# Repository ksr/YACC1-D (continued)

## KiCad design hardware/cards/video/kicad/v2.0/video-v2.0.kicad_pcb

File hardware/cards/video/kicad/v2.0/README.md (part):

# video-v2.0 — KiCad design master for the video card

**The master since 2026-10-22. Ready to order since 2026-10-23 (re-reviewed, every re-review finding applied); not
ordered. Revised 2026-10-26 before the order: the DB9's VSYNC polarity jumper JP4** (below), the board routed again
2026-10-27, with the board-layout rules' silkscreen and cottageworker.com on it; the gerbers exported again
2026-11-03 with every part's value on the silk (silk only) and, the same day, with each power plane in one piece
(16 power pads connected solid, inner layers only: "Planes (2026-11-03)"; `video-v2.0-gerbers.zip`, what to upload:
"Ordering" below). V2.0 is the v1.3 card (`../v1.3/`: 6845, IDT7134 text RAM,
the DOTS jumper, 12 MHz, both fonts in one character generator) plus a **graphics layer**, **every register on I/O ports
PA-PE** and **two PS/2 ports** on an ATmega328P with an **INT jumper**. The design note is `BACKLOG.md` "Video card
V2.0"; the theory `docs/cards/video-v2.md`; the ATmega's firmware `embedded/video-ps2`; the picture and the CPU
side `tools/vidsim.py --card v2.0`.

**Revised 2026-10-22 after the design review** (`hardware/cards/video/reviews/v2.0.md`, its status table at the top):
every HIGH and MEDIUM finding is in the circuit or the firmware, and two features were added - **direct mode** (with
GFX-ON = 0 the CPU owns the graphics RAM: a plain SRAM at any clock the machine runs) and the **text-only build** (the
graphics chips left off, a status bit saying so). **Re-reviewed 2026-10-23** (`hardware/cards/video/reviews/v2.0-r2.md`,
HIGH 0, MED 1, LOW 9, INFO 6; its status table at the top): the MD-60SM side-leg slots widened (R2-1), IC55's socket
clear of its neighbours (R2-2), the bus -RESET buffered (R2-3), the BOM, the README's statements, the silkscreen, the
timing test and the firmware; the rest are driver rules and bench measurements.

Unlike v1.x (Eagle conversions edited in KiCad) this design is **generated**: `v20_netlist.py` is the circuit,
`gen_v20.py` draws the schematic (since 2026-10-24 a root sheet and eight functional sheets with the nets drawn as
wires: "The schematic" below), builds the board and writes `BOM.md`; `build.sh` routes and checks it. Change the circuit in
`v20_netlist.py`, the placement in `gen_v20.py` (`PLACE`), then run `./build.sh` (KiCad 10, Freerouting 1.9 in `FRJAR`,
default `~/freerouting/freerouting.jar`, which opens a window while it runs; `SEEDS="..."` and `MP=` choose the
component orders and passes). `tools/eagle_to_kicad_all.py` never writes here (`MASTER` marker).

## The board

- **218.42 x 113.97 mm** (x 17.747-236.167): the blank V3.2 card's outline lengthened to the sequencer logic V2.1l's
  218 mm, so it needs the same slot space; X1 (DIN 41612) exactly where every card has it, copper keepouts round its
  two screws.
- **4 layers**, the v1.3 / memory card v2.0 stack-up and rules: In1.Cu a solid GND plane, In2.Cu a solid VCC plane, GND
  and VCC never routed (every power pin is a through-hole pad on its plane); signals 0.25 mm, clearance 0.2 mm, vias
  0.8 / 0.4 mm.
- **Placement** (`gen_v20.py` `PLACE`; pin 1 of every DIP at the top left, each 100 nF beside its IC's VCC pin):
  row A (top) the port decode, strobes, the inverters IC46 (beside the control register they mostly serve), the control
  register, status buffers, the PS/2 and graphics latches, WRQ and the video driver IC27; on the left the 600-mil parts (IC15 text RAM, IC17 6845, IC39 62256, IC25 28C64) and IC18 with SV3 /
  RN2; row B the graphics address muxes, display latch and shifter, the ATmega, with the GD pull-ups RN3 standing between
  IC38 and IC42; under IC42 / IC43, on its side, the direct-mode read buffer IC55 (the band under the muxes is left to
  the routing); row C the text pipeline and the gates, with the text-only pads R25 / R26 in the gaps beside IC1; row D
  the clock chain (IC28, IC21, IC20 with Q2, SV4), the remaining gates (IC32 among them, beside the counter whose QC and
  RCO it ORs) and IC54 (turned round, beside J4); the right
  edge DB9 (X2) with its VSYNC polarity jumper JP4 standing beside it (2026-10-26), RCA (J1), the keyboard (J2) and mouse (J3) Mini-DINs with their faces at the board edge, F1, the FTDI header J4 (a legend
  at every pin), the PWR LED. `gen_v20.py place` checks that no two courtyards overlap and, since the re-review (R2-2),
  that every DIP **socket** fits: each socket's outline (the pin rows + 1.3 mm at the sides, the end pins + 1.9 mm at
  the ends: the widest stamped sockets) clear of every other socket and of every other part's pads and body. The
  closest are IC55 (on its side between IC42 above and IC19 / IC1 below) with 0.02 mm to IC42's and 0.10 to IC19's /
  IC1's, IC55 / C59 0.17, IC49 / R12 0.17, IC25 / IC39 0.18 mm; with turned-pin sockets (1.27 mm end walls) IC55 has
  ~0.65 mm. RN3 and C59 stand 0.3 mm left of the middle of their gap for it.
- **Silkscreen** (R2-9; the board-layout rules since 2026-10-24, below): `gen_v20.py silk` writes every legend afresh
  and places it and every reference clear of the other silk, the pads, the edge and every part's body, its own
  included (`silk_texts()`, `silk_place()`). Each IC's type stands on the reference's line ("IC30 74LS138"); the
  jumpers and the LED carry their function and the jumpers each position's meaning. The jack legends "KEYBOARD (PURPLE)" and
  "MOUSE (GREEN)" stand turned beside each jack's body; the Mini-DIN outline is broken round its side-leg pads and stops
  short of the board edge. The card's name stands in the band under the graphics muxes. Since 2026-11-03 every
  resistor, network, capacitor, crystal and the fuse carries its value beside its reference ("R10 1k", "RN3 10k x8",
  "C16 47u", "Y1 16MHz", "F1 0.5A").

## The board-layout rules (2026-10-24)

The rules for every YACC1 board (switches, buttons, LEDs and outside-cable connectors on the front edge, the edge
farthest from the bus connector; every reference readable with the parts fitted, never under a chip, socket or module,
an IC's type beside it; every switch, button and LED labelled with its function, each position of a switch with what
it selects) came after this board was routed and before it was ordered. V2.0 took them on the **silkscreen only**
(2026-10-24): no part moved, the copper and the drills stayed the route of 2026-10-23 (`ed7c060`, order 5, 285 vias).
The VSYNC jumper JP4 (2026-10-26) follows them too: a jumper block near the front edge, its positions labelled. The
board was routed afresh for it ("Results"). Every part's value beside its reference (2026-11-03) came the same way,
on the silkscreen only ("Part values" below).

| Rule | On this board |
|---|---|
| front edge | the DB9 X2, the RCA J1, the PS/2 jacks J2 / J3 and the PWR LED stand at the right-hand edge, opposite X1; the DB9's VSYNC jumper JP4 stands beside the DB9. The FTDI header J4 (the ATmega's programming port) stays where it is, 24 mm in from that edge, with its pin legend: moving it would mean a new route |
| IC type beside the reference | all 40 ICs, on one line with the reference ("IC30 74LS138"): the value of each as the parts list has it, the grade included - IC17 **HD68B45SP / MC68B45P**, IC25 **AT28C64B-15**, IC49 **ATmega328P-P** (2026-11-10; "6845", "28C64" and "ATmega328P" before). Above the IC where there is room, else below it, else turned in the gap beside it (IC19, IC28, IC49 on the left, IC53 on the right); IC49's, too long for its gap on one line, stands there on two ("Labels" below) |
| no reference under a part | every text is kept off every part's body, its own included (its ink off the bodies below, and since 2026-11-10 its whole text box off every part's Fab outline, as `pcb-check` measures it): a DIP's body is the outline of the widest stamped socket (`socket_check`: the pin rows + 1.3 mm, the end pins + 1.9 mm), X1's the DIN 41612 housing (its silk, pads and 2.5 mm past its ends), J1's its outline and pads. R10, R25, R26 and R27 had their references inside their own outline: they now stand beside it. X1's reference left the housing's end (at the top-left corner, x 18.9, y 16.1, until 2026-11-10; now beside the housing with its type, "X1 DIN41612 96"); J1's, hidden by the RCA library footprint, is shown left of the jack. Checked by the texts' ink against every body and socket outline: before, 37 references stood on one - 26 capacitors' on a neighbouring IC's socket wall, IC1's on IC55's socket, IC19's, IC25's and IC54's on their own socket, J2's on J1, R15's and RN3's on IC25's / IC38's socket, R10's, R25's, R26's and R27's on their own body; now none |
| functions and positions | **LED1 PWR**. **JP2 DOTS**, "ON=8 OFF=6" (fitted: 8 dots a character, 64 x 24 with graphics; open: 6 dots, 80 x 24). **JP3 INT-EN**, "ON: PS/2 -INT" / "OFF: NO -INT" (fitted: IC27/D's open collector drives the bus -INT; open: the card never touches -INT). **SV3 BLOCK**, "A15" .. "A12" beside the pairs 1-2 .. 7-8 and "ON=0" (each pair sets the address bit the board select IC18 compares, fitted = 0, open = 1 through RN2; $D000 = 5-6 only). **SV4 DOTCLK**, "XTAL" over pin 1 and "XTAL/2" over pin 3 (1-2: DOTCLOCK the crystal; 2-3: half of it). **JP4 VSYNC**, "+VS CGA" beside pin 1 and "-VS MDA" beside pin 3 (1-2: DB9 pin 9 positive VSYNC, a TV-rate or CGA monitor; 2-3: negative, an MDA monitor; 2026-10-26). The meanings are those of `v20_netlist.py` and `docs/cards/video.md` (sections 3.1, 3.4) and `docs/cards/video-v2.md` |
| part values (2026-11-03) | all 69 resistors, networks, capacitors, crystals and the fuse: the value beside the reference, from `v20_netlist.py` (C16 **47u** for 47u 16V, F1 **0.5A** for 0.5A PTC). 63 on one line or stacked with the reference beside the part; C34 and C38 with the reference beside the part and the value next to it; C3 and C20 with the reference beside the part and the value in the legend "C3 C20: 100n" right of IC55 (no room beside them); C27 and C58 as one block beside their part's neighbour (below) |
| text size | every reference and legend 1.0 mm high with 0.15 mm strokes, JLCPCB's standard legend (the card's name 1.5 mm); "DOTS", "INT-EN" and "TEXT-ONLY" were 0.8 mm. X1's library pin numbers "1" and "32" stay 0.8 mm (0.15 mm strokes; at 1.0 mm "32" meets the housing's outline), JLCPCB's high-precision legend size |

`gen_v20.py silk` places the texts by their ink (not KiCad's taller text box), 0.15 mm from other silk (1.0 mm after an
IC's label), 0.2 mm from pads, 0.4 mm from the edge; an IC's label goes above it, else below, else turned in the gap at
its right, then its left, along that side and within its length. A second run leaves every text where it is.

**Part values (2026-11-03).** The rule for every new card (every part's type or value beside its reference, never
under a fitted part) reached V2.0 as a silkscreen change only, like the rules of 2026-10-24: no part moved, copper and
drills as routed 2026-10-27. Each resistor's, network's, capacitor's, crystal's and the fuse's value is its
`COMPANION` text, placed with the reference by `silk_place()` in this order: on one line or stacked, beside the part
(along one of its sides, within its length); else the reference beside the part and the value beside it too, nearest
the reference; else the value next to the reference wherever that is clear; else the reference beside the part and
the value in a legend with the others' that found no room ("C3 C20: 100n"); else the block at the nearest clear place.
A passive's reference and a value standing apart from it must be nearer their own part than any other non-IC part, so
no text reads as a neighbour's label. A part that ends past the first step is placed earlier in another round (after
the ICs), and the round with the fewest such parts is kept. `gen_v20.py silk` prints the parts that did not take the
first step: C34 and C38 (value apart), C3 and C20 (legend). Adding the values on the first try (the block beside the
part or anywhere) sent ten references 4-14 mm from their parts, C34's beside C52's capacitor among them; the steps
above keep every reference at its own part except two:

- **C27** (IC26's capacitor, between IC26's label, IC55's socket wall and IC19's turned label): "C27 100n" stands
  left of C59's capacitor, under "C59 100n", 3 mm above-left of C27; its reference stood there before too.
- **C58** (IC54's capacitor, at the bottom edge between R10 and IC54's label): "C58 100n" stands under R10, ending at
  C58's left end; its reference stood under R10's end before too, and R10's "R10 1k" stands turned at that end.

Both are 100n like every capacitor round them. No IC label, jumper text or legend moved: their places are those of
2026-10-24 / 2026-10-27, checked text by text.

**Proofs (2026-10-24)**, the silkscreen placed again on the committed board and nothing else rebuilt (no Freerouting,
no `build.sh`):

| Check | Result |
|---|---|
| the board, item by item (pcbnew: 120 footprints' place, orientation, value and footprint; 1,040 pads with their nets, sizes and drills; 5,069 tracks and vias; the zones and keepouts; the outline) | **identical**; the file's changes are the silkscreen texts and the reference fields' places and sizes |
| Gerbers (the commands under "Ordering"), against the export of 2026-10-23 | **only `video-v2.0-F_Silkscreen.gbr` differs**; F_Cu, In1_Cu, In2_Cu, B_Cu, F_Mask, B_Mask, B_Silkscreen, Edge_Cuts, the PTH and NPTH drill files, both drill maps and the job file are identical apart from their date lines |
| `tools/kicad/compare_netlists.py` (schematic vs board) | **MATCH, 216 of 216** net groups |
| `gen_v20.py verify` | **PASS**, 189 key connections |
| `gen_v20.py place` | 120 footprints clear; **sockets PASS** (40), the closest IC42 / IC55 0.02 mm as before |
| DRC (`reports/drc.json`) | 0 unconnected, schematic parity 0, no copper findings; **silk_overlap 0, silk_over_copper 8, silk_edge_clearance 8** (J1's, X1's and X2's library outlines, as before), text_height / text_thickness 0 |
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
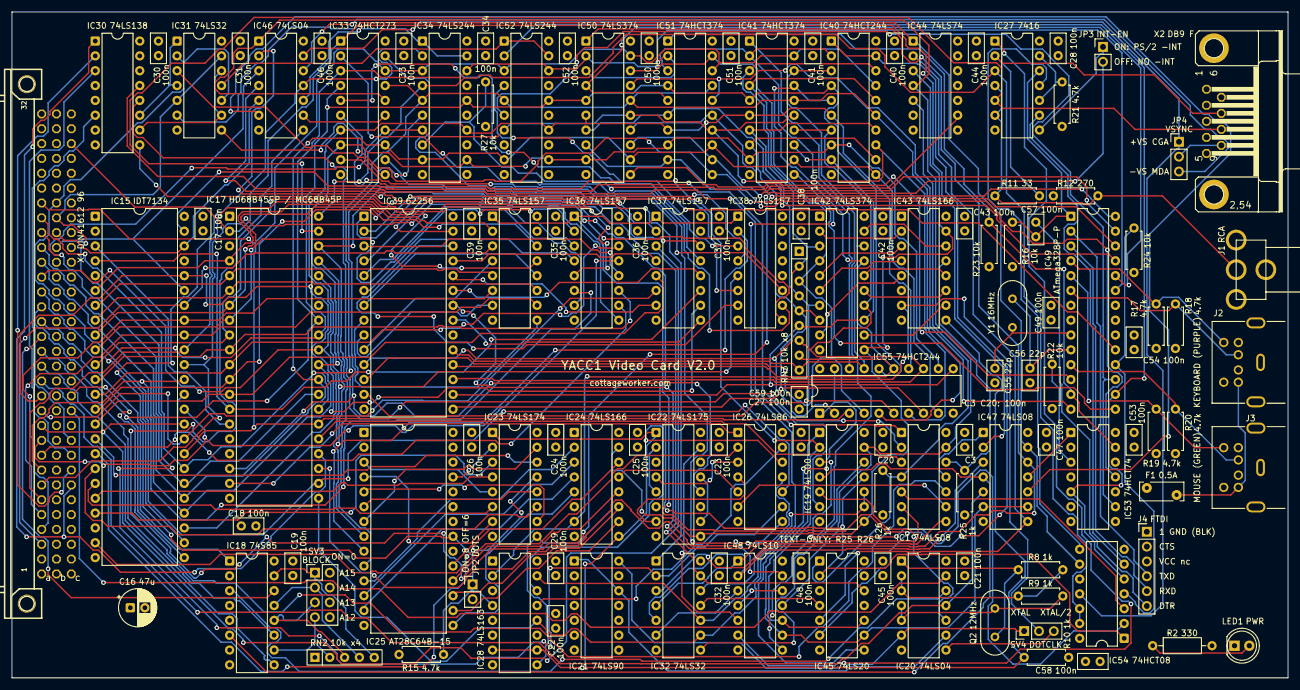
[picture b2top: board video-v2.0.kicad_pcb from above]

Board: 4 copper layers, 218.4 x 114.0 mm, 121 parts (0 on the bottom side), 219 nets.

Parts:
C3, C17, C18, C19, C20, C21, C22, C23, C24, C25, C26, C27, C28, C29, C30, C31, C32, C33, C34, C35, C36, C37, C38, C39, C40, C41, C42, C43, C44, C45, C46, C47, C48, C49, C50, C51, C52, C53, C54, C57, C58, C59: 100n; C_Disc_D5.0mm_W2.5mm_P2.50mm
C16: 47u 16V; CP_Radial_D6.3mm_P2.50mm
C55, C56: 22p; C_Disc_D5.0mm_W2.5mm_P2.50mm
F1: 0.5A PTC; Fuse_Bourns_MF-RHT050
IC1: 74ALS08; DIP-14_W7.62mm
IC15: IDT7134; DIP-48_W15.24mm
IC17: HD68B45SP / MC68B45P; DIP-40_W15.24mm
IC18: 74S85; DIP-16_W7.62mm
IC19: 74LS00; DIP-14_W7.62mm
IC20, IC46: 74LS04; DIP-14_W7.62mm
IC21: 74LS90; DIP-14_W7.62mm
IC22: 74LS175; DIP-16_W7.62mm
IC23: 74LS174; DIP-16_W7.62mm
IC24, IC43: 74LS166; DIP-16_W7.62mm
IC25: AT28C64B-15; DIP-28_W15.24mm
IC26: 74LS86; DIP-14_W7.62mm
IC27: 7416; DIP-14_W7.62mm
IC28: 74LS163; DIP-16_W7.62mm
IC30: 74LS138; DIP-16_W7.62mm
IC31, IC32: 74LS32; DIP-14_W7.62mm
IC33: 74HCT273; DIP-20_W7.62mm
IC34, IC52: 74LS244; DIP-20_W7.62mm
IC35, IC36, IC37, IC38: 74LS157; DIP-16_W7.62mm
IC39: 62256; DIP-28_W15.24mm
IC40, IC55: 74HCT244; DIP-20_W7.62mm
IC41, IC51: 74HCT374; DIP-20_W7.62mm
IC42, IC50: 74LS374; DIP-20_W7.62mm
IC44: 74LS74; DIP-14_W7.62mm
IC45: 74LS20; DIP-14_W7.62mm
IC47: 74LS08; DIP-14_W7.62mm
IC48: 74LS10; DIP-14_W7.62mm
IC49: ATmega328P-P; DIP-28_W7.62mm
IC53: 74HCT74; DIP-14_W7.62mm
IC54: 74HCT08; DIP-14_W7.62mm
J1: RCA
J2: KEYBOARD; MiniDIN6_MD-60SM
J3: MOUSE; MiniDIN6_MD-60SM
J4: FTDI; PinHeader_1x06_P2.54mm_Vertical
JP2: DOTS 8=ON; PinHeader_1x02_P2.54mm_Vertical
JP3: INT-EN; PinHeader_1x02_P2.54mm_Vertical
JP4: VSYNC +/-; PinHeader_1x03_P2.54mm_Vertical
LED1: PWR; LED_D5.0mm
Q2: 12MHz; Crystal_HC49-U_Vertical
R2: 330; R_Axial_DIN0207_L6.3mm_D2.5mm_P10.16mm_Horizontal
R8, R9, R10, R25, R26: 1k; R_Axial_DIN0207_L6.3mm_D2.5mm_P7.62mm_Horizontal
R11: 33; R_Axial_DIN0207_L6.3mm_D2.5mm_P7.62mm_Horizontal
R12: 270; R_Axial_DIN0207_L6.3mm_D2.5mm_P7.62mm_Horizontal
R15, R17, R18, R19, R20, R21: 4.7k; R_Axial_DIN0207_L6.3mm_D2.5mm_P7.62mm_Horizontal
R16, R22, R23, R24, R27: 10k; R_Axial_DIN0207_L6.3mm_D2.5mm_P7.62mm_Horizontal
RN2: 10k x4; R_Array_SIP5
RN3: 10k x8; R_Array_SIP9
SV3: BLOCK; PinHeader_2x04_P2.54mm_Vertical
SV4: DOTCLK; PinHeader_1x03_P2.54mm_Vertical
X1: DIN41612 96; FABC96R
X2: DB9 F; F09HP
Y1: 16MHz; Crystal_HC49-U_Vertical

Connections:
/-INT: JP3.2, X1.C13
/-IO-RD: IC26.9, IC31.5, IC31.13, IC32.2, X1.B25
/-IO-WR: IC17.22, IC26.10, IC31.2, IC31.10, X1.B26
/-MEM-RD: IC15.43, IC46.3, X1.B23
/-MEM-WR: IC15.46, IC46.5, X1.B24
/-RESET: IC17.2, IC33.1, IC44.1, IC47.13, IC54.9, X1.C30
/-VMA: IC20.13, X1.C12
/ADDR0: IC15.42, IC35.3, X1.A3
/ADDR1: IC15.41, IC35.6, X1.A4
/ADDR2: IC15.40, IC35.10, X1.A5
/ADDR3: IC15.39, IC35.13, X1.A6
/ADDR4: IC15.38, IC36.3, X1.A7
/ADDR5: IC15.37, IC36.6, X1.A8
/ADDR6: IC15.36, IC36.10, X1.A9
/ADDR7: IC15.35, IC36.13, X1.A10
/ADDR8: IC15.34, IC37.3, X1.A11
/ADDR9: IC15.33, IC37.6, X1.A12
/ADDR10: IC15.44, IC37.10, X1.A13
/ADDR11: IC20.11, IC47.5, X1.A14
/ADDR12: IC18.9, X1.A15
/ADDR13: IC18.11, X1.A16
/ADDR14: IC18.14, X1.A17
/ADDR15: IC18.1, X1.A18
/ATTR1: IC22.4, IC26.3
/ATTR2: IC22.2, IC22.5
/ATTR3: IC22.7, IC26.4
/BOARDSEL: IC18.6, IC19.4, IC47.4
/BUSY: IC49.17, IC52.6, IC53.9
/CA3: IC23.15, IC25.7
/CA4: IC23.12, IC25.6
/CA5: IC23.10, IC25.5
/CA6: IC23.7, IC25.4
/CA7: IC23.5, IC25.3
/CA8: IC23.2, IC25.25
/CG0: IC24.2, IC25.11
/CG1: IC24.3, IC25.12
/CG2: IC24.4, IC25.13
/CG3: IC24.5, IC25.15
/CG4: IC24.10, IC25.16
/CG5: IC24.11, IC25.17
/CG6: IC24.12, IC25.18
/CG7: IC24.14, IC25.19
/CHARCLOCK: IC19.8, IC22.9, IC23.9, IC24.15, IC28.9, IC42.11, IC43.15, IC44.3
/CMDCLK: IC31.8, IC51.11, IC53.11
/CNTEN: IC22.1, IC23.1, IC24.9, IC28.7, IC28.10, IC43.9, R10.1
/CNTQA: IC26.12, IC28.14
/CNTQB: IC26.13, IC28.13
/CPAGE: IC33.9, IC38.10
/CRTCCLOCK: IC17.21, IC28.12, IC32.9, IC41.11
/CRTCCS: IC1.3, IC17.25
/CRTCE: IC17.23, IC26.8
/CTLCLK: IC31.3, IC33.11
/CURSOR: IC17.19, IC26.1
/DATA0: IC15.25, IC17.33, IC33.3, IC34.18, IC40.2, IC41.2, IC50.2, IC51.3, IC52.18, IC55.18, X1.A19
/DATA1: IC15.26, IC17.32, IC33.4, IC34.16, IC40.4, IC41.5, IC50.5, IC51.4, IC52.16, IC55.16, X1.A20
/DATA2: IC15.27, IC17.31, IC33.7, IC34.14, IC40.6, IC41.6, IC50.6, IC51.7, IC52.14, IC55.14, X1.A21
/DATA3: IC15.28, IC17.30, IC33.8, IC34.12, IC40.8, IC41.9, IC50.9, IC51.8, IC52.12, IC55.12, X1.A22
/DATA4: IC15.29, IC17.29, IC33.13, IC34.9, IC40.11, IC41.12, IC50.12, IC51.13, IC52.9, IC55.9, X1.A23
/DATA5: IC15.30, IC17.28, IC33.14, IC34.7, IC40.13, IC41.15, IC50.15, IC51.14, IC52.7, IC55.7, X1.A24
/DATA6: IC15.31, IC17.27, IC33.17, IC34.5, IC40.15, IC41.16, IC50.16, IC51.17, IC52.5, IC55.5, X1.A25
/DATA7: IC15.32, IC17.26, IC33.18, IC34.3, IC40.17, IC41.19, IC50.19, IC51.18, IC52.3, IC55.3, X1.A26
/DB9VS: JP4.2, X2.9
/DE: IC17.18, IC22.12, IC34.6
/DE2: IC22.10, IC22.13
/DE3: IC22.15, IC48.5
/DOTCLKH: IC20.8, SV4.3
/DOTCLOCK: IC24.7, IC28.2, IC43.7, SV4.2
/DOTS: IC25.21, IC28.4, IC34.2, IC46.11, JP2.1, R15.2
/DPAGE: IC33.12, IC38.11
/DRDOE: IC45.8, IC55.1, IC55.19
/EIGHT: IC46.10, IC47.2
/FDTR: C57.1, J4.6
/FRX: IC49.3, J4.5
/FTX: IC49.2, J4.4
/FULL: IC49.16, IC52.2, IC53.5, IC54.5
/FULLCLR: IC47.11, IC53.1
/GA0: IC35.4, IC39.10
/GA1: IC35.7, IC39.9
/GA2: IC35.9, IC39.8
/GA3: IC35.12, IC39.7
/GA4: IC36.4, IC39.6
/GA5: IC36.7, IC39.5
/GA6: IC36.9, IC39.4
/GA7: IC36.12, IC39.3
/GA8: IC37.4, IC39.25
/GA9: IC37.7, IC39.24
/GA10: IC37.9, IC39.21
/GA11: IC37.12, IC39.23
/GA12: IC38.4, IC39.2
/GA13: IC38.7, IC39.26
/GA14: IC38.9, IC39.1
/GD0: IC39.11, IC40.18, IC41.3, IC42.3, IC55.2, RN3.2
/GD1: IC39.12, IC40.16, IC41.4, IC42.4, IC55.4, RN3.3
/GD2: IC39.13, IC40.14, IC41.7, IC42.7, IC55.6, RN3.4
/GD3: IC39.15, IC40.12, IC41.8, IC42.8, IC55.8, RN3.5
/GD4: IC39.16, IC40.9, IC41.13, IC42.13, IC55.11, RN3.6
/GD5: IC39.17, IC40.7, IC41.14, IC42.14, IC55.13, RN3.7
/GD6: IC39.18, IC40.5, IC41.17, IC42.17, IC55.15, RN3.8
/GD7: IC39.19, IC40.3, IC41.18, IC42.18, IC55.17, RN3.9
/GDA: IC1.11, IC47.1
/GDG: IC32.5, IC47.3, IC48.2
/GDOT: IC1.12, IC43.13, R25.1
/GFXON: IC1.13, IC19.13, IC33.16, IC44.4, IC46.1, IC48.11
/GL0: IC42.2, IC43.2
/GL1: IC42.5, IC43.3
/GL2: IC42.6, IC43.4
/GL3: IC42.9, IC43.5
/GL4: IC42.12, IC43.10
/GL5: IC42.15, IC43.11
/GL6: IC42.16, IC43.12
/GL7: IC42.19, IC43.14
/GOR: IC32.6, IC48.3
/GRDOE: IC19.3, IC54.2
/GSEL: IC19.1, IC45.9, IC47.6, IC47.9, IC48.9
/GWE: IC39.27, IC40.1, IC40.19, IC45.6
/GWR: IC44.2, IC45.5, IC47.8
/HSYNC: IC17.39, IC27.5, X2.8
/INTG: IC27.9, IC54.6
/INTOC: IC27.8, JP3.1
/INTREQ: IC49.18, IC54.4, R24.1
/IO-ADDR0: IC17.24, IC30.1, X1.C7
/IO-ADDR1: IC30.2, X1.C8
/IO-ADDR2: IC30.3, X1.C9
/IO-ADDR3: IC30.6, X1.C10
/KCLK: IC49.4, J2.5, R17.1
/KDAT: IC49.6, J2.1, R18.1
/LDDATA: IC49.12, IC50.11, IC53.3, R22.1
/MCLK: IC49.5, J3.5, R19.1
/MD0: IC49.23, IC50.3, IC51.2
/MD1: IC49.24, IC50.4, IC51.5
/MD2: IC49.25, IC50.7, IC51.6
/MD3: IC49.26, IC50.8, IC51.9
/MD4: IC49.27, IC50.13, IC51.12
/MD5: IC49.28, IC50.14, IC51.15
/MD6: IC49.14, IC50.17, IC51.16
/MD7: IC49.15, IC50.18, IC51.19
/MDAT: IC49.11, J3.1, R20.1
/MEMRD: IC19.2, IC45.10, IC46.4, IC48.10
/MEMWR: IC46.6, IC47.10
/MRST: C57.2, IC27.12, IC49.1, R16.1
/NADDR11: IC19.5, IC20.10
/NBOTH: IC48.4, IC48.12
/NGFX: IC32.13, IC45.12, IC46.2
/NMUX: IC19.11, IC35.1, IC36.1, IC37.1, IC38.1, IC45.2, IC54.1
/NVSYNC: IC46.12, JP4.3
/OEY: IC1.5, IC54.3
/OSCIN: IC20.1, Q2.1, R8.1
/OSCMID: IC20.2, IC20.3, R8.2, R9.1
/OSCOUT: IC20.4, IC20.5, Q2.2, R9.2
/PDOE: IC32.3, IC47.12, IC50.1
/PLANE0: IC33.2, IC37.13
/PLANE1: IC33.5, IC38.3
/PLANE2: IC33.6, IC38.6
/PS2VCC: F1.2, J2.4, J3.4
/PSEL_A: IC1.1, IC30.13
/PSEL_B: IC1.2, IC30.12
/PSEL_C: IC30.11, IC31.1, IC31.4
/PSEL_D: IC30.10, IC31.9, IC31.12
/PSEL_E: IC30.9, IC32.1
/PSTOE: IC31.11, IC52.1, IC52.19
/PWRLED: LED1.2, R2.1
/QCR: IC19.12, IC32.8
/RCO: IC19.9, IC19.10, IC28.15, IC32.10
/RDCMD: IC49.13, IC51.1, IC53.13, R23.1
/RESETB: IC27.11, IC54.8
/RESETH: IC27.10, IC27.13, R21.1
/SEL0: IC18.10, RN2.2, SV3.7
/SEL1: IC18.12, RN2.3, SV3.5
/SEL2: IC18.13, RN2.4, SV3.3
/SEL3: IC18.15, RN2.5, SV3.1
/SRC: IC49.19, IC52.4
/SRDOE: IC41.1, IC48.8
/STATOE: IC31.6, IC34.1, IC34.19
/SYNC: IC27.4, IC27.6, J1.C1, R11.1, R12.2
/TD: IC1.9, IC26.6
/TDG: IC1.8, IC32.4, IC48.1
/TDOT: IC24.13, IC26.5
/TEXTOFF: IC33.15, IC46.9
/TEXTON: IC1.10, IC46.8
/TXTCE: IC15.47, IC19.6
/TXTONLY: IC34.8, IC44.9, R27.1
/VADDR0: IC15.6, IC17.4, IC35.2
/VADDR1: IC15.7, IC17.5, IC35.5
/VADDR2: IC15.8, IC17.6, IC35.11
/VADDR3: IC15.9, IC17.7, IC35.14
/VADDR4: IC15.10, IC17.8, IC36.2
/VADDR5: IC15.11, IC17.9, IC36.5
/VADDR6: IC15.12, IC17.10, IC36.11
/VADDR7: IC15.13, IC17.11, IC36.14
/VADDR8: IC15.14, IC17.12, IC37.2
/VADDR9: IC15.15, IC17.13, IC37.5
/VADDR10: IC15.4, IC17.14, IC37.11
/VADDR11: IC15.3, IC17.15
/VDATA0: IC15.16, IC23.14
/VDATA1: IC15.17, IC23.13
/VDATA2: IC15.18, IC23.11
/VDATA3: IC15.19, IC23.6
/VDATA4: IC15.20, IC23.4
/VDATA5: IC15.21, IC23.3
/VDATA7: IC15.23, IC26.2
/VIDEO: IC27.2, R11.2, X2.7
/VIDN: IC27.1, IC48.6
/VMA: IC18.3, IC20.12
/VROWS0: IC17.38, IC25.10, IC37.14
/VROWS1: IC17.37, IC25.9, IC38.2
/VROWS2: IC17.36, IC25.8, IC38.5
/VSBUF: IC46.13, IC54.11, JP4.1
/VSYNC: IC17.40, IC27.3, IC34.4, IC54.12, IC54.13
/WEPH: IC26.11, IC32.12
/WEPH2: IC32.11, IC45.4
/WRQ: IC1.4, IC44.5, IC45.1, R26.1
/WSLOT: IC1.6, IC39.22
/XORM: IC33.19, IC48.13
/XT1: C55.1, IC49.9, Y1.1
/XT2: C56.1, IC49.10, Y1.2
/XTAL: IC20.6, IC21.14, SV4.1
/XTALDIV2: IC20.9, IC21.1, IC21.12
GND: C3.2, C16.2, C17.2, C18.2, C19.2, C20.2, C21.2, C22.2, C23.2, C24.2, C25.2, C26.2, C27.2, C28.2, C29.2, C30.2, C31.2, C32.2, C33.2, C34.2, C35.2, C36.2, C37.2, C38.2, C39.2, C40.2, C41.2, C42.2, C43.2, C44.2, C45.2, C46.2, C47.2, C48.2, C49.2, C50.2, C51.2, C52.2, C53.2, C54.2, C55.2, C56.2, C58.2, C59.2, IC1.7, IC15.1, IC15.5, IC15.24, IC15.45, IC17.1, IC17.3, IC18.2, IC18.4, IC18.8, IC19.7, IC20.7, IC21.2, IC21.3, IC21.6, IC21.7, IC21.10, IC22.8, IC23.8, IC24.1, IC24.6, IC24.8, IC25.2, IC25.14, IC25.20, IC25.22, IC25.23, IC25.24, IC26.7, IC27.7, IC28.3, IC28.5, IC28.8, IC30.4, IC30.5, IC30.8, IC31.7, IC32.7, IC33.10, IC34.10, IC34.13, IC34.17, IC35.8, IC35.15, IC36.8, IC36.15, IC37.8, IC37.15, IC38.8, IC38.13, IC38.14, IC38.15, IC39.14, IC39.20, IC40.10, IC41.10, IC42.1, IC42.10, IC43.1, IC43.6, IC43.8, IC44.7, IC44.11, IC44.12, IC44.13, IC45.7, IC46.7, IC47.7, IC48.7, IC49.8, IC49.22, IC50.10, IC51.10, IC52.8, IC52.10, IC52.11, IC52.13, IC52.15, IC52.17, IC53.7, IC54.7, IC55.10, J1.S1, J1.S2, J1.S3, J2.3, J2.S, J3.3, J3.S, J4.1, J4.2, JP2.2, LED1.1, R24.2, R25.2, R26.2, SV3.2, SV3.4, SV3.6, SV3.8, X1.A1, X1.A32, X1.B1, X1.B32, X1.C1, X1.C32, X2.1, X2.2, X2.G1, X2.G2
VCC: C3.1, C16.1, C17.1, C18.1, C19.1, C20.1, C21.1, C22.1, C23.1, C24.1, C25.1, C26.1, C27.1, C28.1, C29.1, C30.1, C31.1, C32.1, C33.1, C34.1, C35.1, C36.1, C37.1, C38.1, C39.1, C40.1, C41.1, C42.1, C43.1, C44.1, C45.1, C46.1, C47.1, C48.1, C49.1, C50.1, C51.1, C52.1, C53.1, C54.1, C58.1, C59.1, F1.1, IC1.14, IC15.2, IC15.48, IC17.20, IC18.16, IC19.14, IC20.14, IC21.5, IC22.16, IC23.16, IC24.16, IC25.27, IC25.28, IC26.14, IC27.14, IC28.1, IC28.6, IC28.16, IC30.16, IC31.14, IC32.14, IC33.20, IC34.11, IC34.15, IC34.20, IC35.16, IC36.16, IC37.16, IC38.16, IC39.28, IC40.20, IC41.20, IC42.20, IC43.16, IC44.10, IC44.14, IC45.13, IC45.14, IC46.14, IC47.14, IC48.14, IC49.7, IC49.20, IC50.20, IC51.20, IC52.20, IC53.2, IC53.4, IC53.10, IC53.12, IC53.14, IC54.10, IC54.14, IC55.20, R2.2, R10.2, R12.1, R15.1, R16.2, R17.2, R18.2, R19.2, R20.2, R21.2, R22.2, R23.2, R27.2, RN2.1, RN3.1, X1.A2, X1.A31, X1.B2, X1.B31, X1.C2, X1.C31

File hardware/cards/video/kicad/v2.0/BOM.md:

# Video card V2.0 - bill of materials

GENERATED by `gen_v20.py bom` from `v20_netlist.py` (2026-10-26) - do not edit. 121 parts. Buy every IC in a socket (the 6845, the IDT7134, the 28C64, the 62256 and the ATmega at least); the placement leaves room for stamped sockets with end walls up to 1.9 mm (R2-2, `gen_v20.py place`). **Text-only build** (the recommended first build, README): leave off the parts marked *off*, fit the ones marked *only*.

| Qty | Value | Footprint | References | Text-only | Buy / note |
|---|---|---|---|---|---|
| 30 | 100n | C_Disc_D5.0mm_W2.5mm_P2.50mm | C3, C17, C18, C19, C20, C21, C22, C23, C24, C25, C26, C27, C28, C29, C30, C31, C32, C33, C34, C46, C47, C48, C49, C50, C51, C52, C53, C54, C57, C58 |  | ceramic X7R, 50 V, 2.5 mm lead spacing |
| 1 | 47u 16V | CP_Radial_D6.3mm_P2.50mm | C16 |  | 47 uF electrolytic, 16 V or more, radial 6.3 mm, 2.5 mm pitch (R2-7) |
| 12 | 100n | C_Disc_D5.0mm_W2.5mm_P2.50mm | C35, C36, C37, C38, C39, C40, C41, C42, C43, C44, C45, C59 | off | ceramic X7R, 50 V, 2.5 mm lead spacing |
| 2 | 22p | C_Disc_D5.0mm_W2.5mm_P2.50mm | C55, C56 |  | ceramic C0G (NP0), 50 V, 2.5 mm lead spacing |
| 1 | 0.5A PTC | Fuse_Bourns_MF-RHT050 | F1 |  | Bourns MF-RHT050 (0.5 A hold, radial) |
| 1 | 74ALS08 | DIP-14_W7.62mm | IC1 |  |  |
| 1 | IDT7134 | DIP-48_W15.24mm | IC15 |  | IDT7134 (SA/LA, 55-90 ns, DIP-48), or the V1.0 card's chip |
| 1 | HD68B45SP / MC68B45P | DIP-40_W15.24mm | IC17 |  | HD68B45SP (Hitachi) or MC68B45P (Motorola), the 2 MHz (B) bus grade: a 6 MHz CPU's OUT gives E 333 ns high (PWEH 220 ns in the B grade, 450 in the 1 MHz grade) and 6-dot mode needs its clock-low time (V2-11, R2-7). HD6845SP / MC6845P (the 1 MHz grades) only with a 1 MHz CPU and the V2-11 clock-low check in 6-dot mode. Hitachi's letters (HD6845S / HD68A45S / HD68B45S = 1.0 / 1.5 / 2.0 MHz) to verify on the part's data sheet |
| 1 | 74S85 | DIP-16_W7.62mm | IC18 |  | 74S85 (the V1.x card's; a 74LS85 also works: see the README) |
| 1 | 74LS00 | DIP-14_W7.62mm | IC19 |  | 74LS00; a 74ALS00 adds a little more CHARCLOCK margin (R3-1) |
| 2 | 74LS04 | DIP-14_W7.62mm | IC20, IC46 |  |  |
| 1 | 74LS90 | DIP-14_W7.62mm | IC21 |  |  |
| 1 | 74LS175 | DIP-16_W7.62mm | IC22 |  |  |
| 1 | 74LS174 | DIP-16_W7.62mm | IC23 |  |  |
| 1 | 74LS166 | DIP-16_W7.62mm | IC24 |  |  |
| 1 | AT28C64B-15 | DIP-28_W15.24mm | IC25 |  | AT28C64B-15PU (Microchip), 150 ns, burned with chargen-v20.bin (minipro -p AT28C64B -u -P -w) |
| 1 | 74LS86 | DIP-14_W7.62mm | IC26 |  |  |
| 1 | 7416 | DIP-14_W7.62mm | IC27 |  |  |
| 1 | 74LS163 | DIP-16_W7.62mm | IC28 |  | 74F163A or 74ALS163B (same pinout; R3-1: with a 74LS163, CHARCLOCK's set-up to the 74LS166s' SH/-LD is ~3 ns at worst-case delays, ~24 ns typical); keep a spare 74F163 |
| 1 | 74LS138 | DIP-16_W7.62mm | IC30 |  |  |
| 2 | 74LS32 | DIP-14_W7.62mm | IC31, IC32 |  |  |
| 1 | 74HCT273 | DIP-20_W7.62mm | IC33 |  |  |
| 2 | 74LS244 | DIP-20_W7.62mm | IC34, IC52 |  |  |
| 4 | 74LS157 | DIP-16_W7.62mm | IC35, IC36, IC37, IC38 | off |  |
| 1 | 62256 | DIP-28_W15.24mm | IC39 | off | AS6C62256-55PCN (Alliance, 55 ns, 600-mil DIP-28): -55 recommended (current production); a slower 62256 works in direct mode up to the machine's 6 MHz and in slot mode in 8-dot mode (R2-8); not a 300-mil 'skinny' 62256 |
| 1 | 74HCT244 | DIP-20_W7.62mm | IC40 | off |  |
| 1 | 74HCT374 | DIP-20_W7.62mm | IC41 | off | 74HCT374; a 74ACT374 (24 mA) if DATA0's low level during a window read is above 0.5 V (R2-6) |
| 1 | 74LS374 | DIP-20_W7.62mm | IC42 | off |  |
| 1 | 74LS166 | DIP-16_W7.62mm | IC43 | off |  |
| 1 | 74LS74 | DIP-14_W7.62mm | IC44 | off |  |
| 1 | 74LS20 | DIP-14_W7.62mm | IC45 | off |  |
| 1 | 74LS08 | DIP-14_W7.62mm | IC47 |  |  |
| 1 | 74LS10 | DIP-14_W7.62mm | IC48 |  |  |
| 1 | ATmega328P-P | DIP-28_W7.62mm | IC49 |  | ATmega328P-PU with the Arduino Uno bootloader burned (ISP) before fitting |
| 1 | 74LS374 | DIP-20_W7.62mm | IC50 |  |  |
| 1 | 74HCT374 | DIP-20_W7.62mm | IC51 |  |  |
| 1 | 74HCT74 | DIP-14_W7.62mm | IC53 |  |  |
| 1 | 74HCT08 | DIP-14_W7.62mm | IC54 |  |  |
| 1 | 74HCT244 | DIP-20_W7.62mm | IC55 | off | 74HCT244; a 74ACT244 (24 mA) if DATA0's low level during a window read is above 0.5 V (R2-6) |
| 1 | RCA | RCA | J1 |  | RCA jack, right-angle PCB mount: the V1.0 card's part (the footprint is V1.0's) |
| 1 | KEYBOARD | MiniDIN6_MD-60SM | J2 |  | Same Sky (CUI Devices) MD-60SM, date code after 2022-03-03 (the footprint follows that layout) |
| 1 | MOUSE | MiniDIN6_MD-60SM | J3 |  | Same Sky (CUI Devices) MD-60SM, date code after 2022-03-03 |
| 1 | FTDI | PinHeader_1x06_P2.54mm_Vertical | J4 |  | 1x6 pin header; a 5 V FTDI cable (TTL-232R-5V) or a 5 V FTDI Basic |
| 1 | DOTS 8=ON | PinHeader_1x02_P2.54mm_Vertical | JP2 |  |  |
| 1 | INT-EN | PinHeader_1x02_P2.54mm_Vertical | JP3 |  |  |
| 1 | VSYNC +/- | PinHeader_1x03_P2.54mm_Vertical | JP4 |  | 1x3 pin header and a shunt: 1-2 (+VSYNC) for a TV-rate or CGA monitor, 2-3 (-VSYNC) for an MDA monitor |
| 1 | PWR | LED_D5.0mm | LED1 |  |  |
| 1 | 12MHz | Crystal_HC49-U_Vertical | Q2 |  | 12 MHz, HC-49/U |
| 1 | 330 | R_Axial_DIN0207_L6.3mm_D2.5mm_P10.16mm_Horizontal | R2 |  |  |
| 3 | 1k | R_Axial_DIN0207_L6.3mm_D2.5mm_P7.62mm_Horizontal | R8, R9, R10 |  |  |
| 1 | 33 | R_Axial_DIN0207_L6.3mm_D2.5mm_P7.62mm_Horizontal | R11 |  |  |
| 1 | 270 | R_Axial_DIN0207_L6.3mm_D2.5mm_P7.62mm_Horizontal | R12 |  |  |
| 6 | 4.7k | R_Axial_DIN0207_L6.3mm_D2.5mm_P7.62mm_Horizontal | R15, R17, R18, R19, R20, R21 |  |  |
| 5 | 10k | R_Axial_DIN0207_L6.3mm_D2.5mm_P7.62mm_Horizontal | R16, R22, R23, R24, R27 |  |  |
| 2 | 1k | R_Axial_DIN0207_L6.3mm_D2.5mm_P7.62mm_Horizontal | R25, R26 | only |  |
| 1 | 10k x4 | R_Array_SIP5 | RN2 |  | 10k x4 BUSSED, pin 1 common, 5-pin SIP (e.g. Bourns 4605X-101-103LF); not an isolated network, which would leave SEL0-3 without pull-ups (R3-15) |
| 1 | 10k x8 | R_Array_SIP9 | RN3 | off | 10k x8 BUSSED, pin 1 common, 9-pin SIP (e.g. Bourns 4609X-101-103LF); not an isolated network, which would leave GD0-7 without pull-ups (R3-15) |
| 1 | BLOCK | PinHeader_2x04_P2.54mm_Vertical | SV3 |  |  |
| 1 | DOTCLK | PinHeader_1x03_P2.54mm_Vertical | SV4 |  |  |
| 1 | DIN41612 96 | FABC96R | X1 |  |  |
| 1 | DB9 F | F09HP | X2 |  | DE-9 female, right-angle PCB mount: the V1.0 card's part, or check a new one's pin pitch first - the F09HP footprint is 2.74 mm pitch, 2.54 mm between rows (most DE-9s 2.77 / 2.84 mm; R3-16) |
| 1 | 16MHz | Crystal_HC49-U_Vertical | Y1 |  | 16 MHz, HC-49/U, parallel resonant, 18-20 pF load (for C55 / C56 22 pF, as on an Arduino Uno) |

Fitted in both builds: everything not marked *off* or *only*. The text-only build leaves off 25 parts (IC35, IC36, IC37, IC38, IC39, IC40, IC41, IC42, IC43, IC44, IC45, IC55, RN3, C35, C36, C37, C38, C39, C40, C41, C42, C43, C44, C45, C59) and fits R25, R26.

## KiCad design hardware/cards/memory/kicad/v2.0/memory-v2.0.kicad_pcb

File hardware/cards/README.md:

# hardware/cards

One folder per card: README.md, kicad/ (current), eagle/<rev>/ (deprecated), docs/, bom/.

_Contents migrated 2026-09-19; MIGRATION.md at the repo root says which copy each item came from._

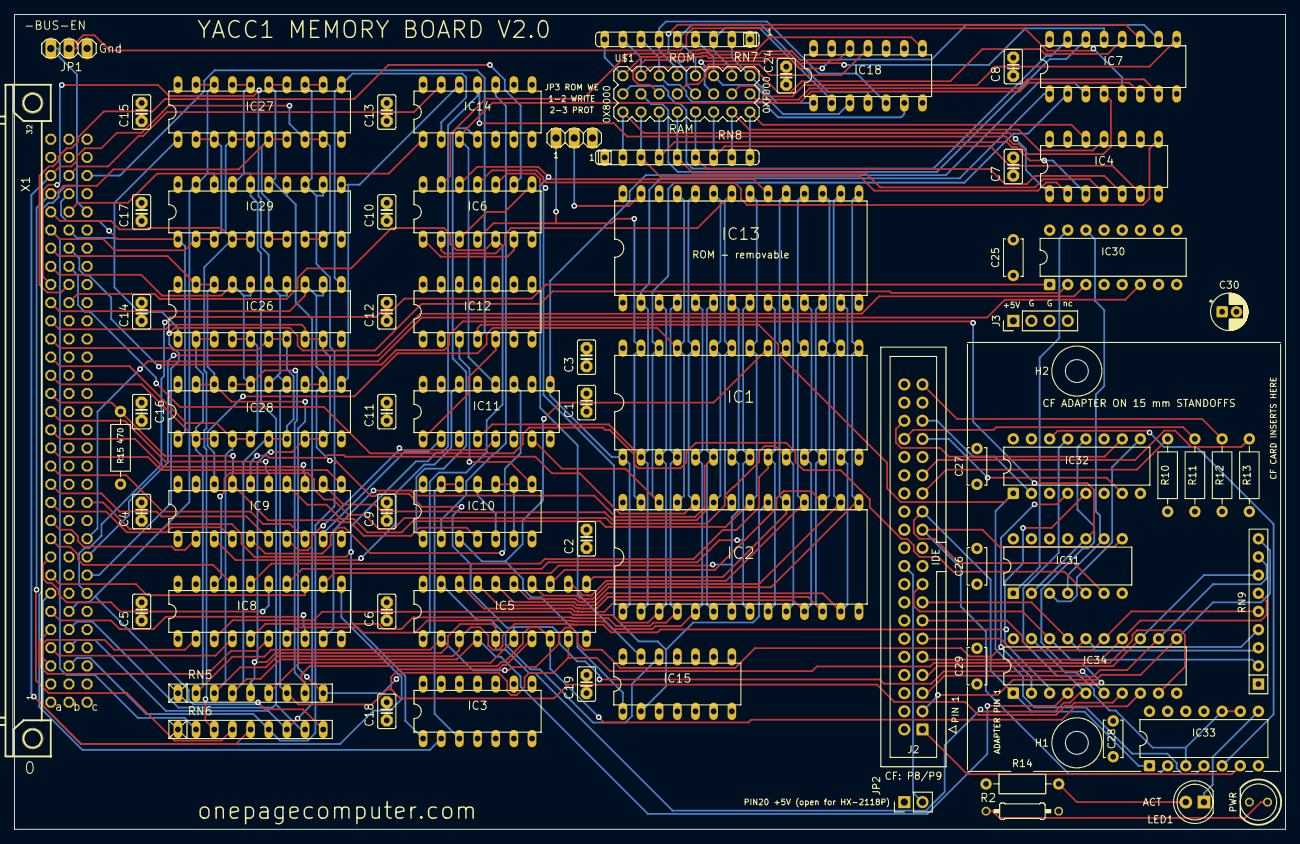
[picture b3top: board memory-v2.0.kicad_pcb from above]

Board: 4 copper layers, 177.8 x 114.0 mm, 74 parts (0 on the bottom side), 149 nets.

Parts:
C1, C2, C3, C4, C5, C6, C7, C8, C9, C10, C11, C12, C13, C14, C15, C16, C17, C18, C19, C24: C025-025X050
C25, C26, C27, C28, C29: 100n; C_Disc_D5.0mm_W2.5mm_P5.00mm
C30: 10u; CP_Radial_D5.0mm_P2.00mm
H1, H2: M3 standoff 15 mm (CF adapter); MountingHole_3.2mm_M3
IC1, IC2, IC13: DIL28-6
IC3: 74LS32N; DIL14
IC4, IC18: 74ALS30N; DIL14
IC5: 74LS245N; DIL20
IC6, IC14: 74LS04N; DIL14
IC7: 74LS138N; DIL16
IC8, IC9: 74LS244N; DIL20
IC10: 74ALS00N; DIL14
IC11: 74LS157N; DIL16
IC12: 74LS74N; DIL14
IC15: 74ALS11N; DIL14
IC26, IC27, IC28, IC29: 74LS374N; DIL20
IC30: 74LS138; DIP-16_W7.62mm
IC31: 74LS32; DIP-14_W7.62mm
IC32: 74LS175; DIP-16_W7.62mm
IC33: 74LS08; DIP-14_W7.62mm
IC34: 74LS245; DIP-20_W7.62mm
J2: IDE 40; IDC-Header_2x20_P2.54mm_Vertical
J3: POWER; PinHeader_1x04_P2.54mm_Vertical
JP1: 1X03
JP2: PIN20 5V; PinHeader_1x02_P2.54mm_Vertical
JP3: PINHD-1X3; 1X03
LED1: ACT yellow; LED_D5.0mm
PWR0: LED5MM
R2: 330; 0207_10
R10, R11, R12, R13: 10k; R_Axial_DIN0207_L6.3mm_D2.5mm_P10.16mm_Horizontal
R14: 1k; R_Axial_DIN0207_L6.3mm_D2.5mm_P10.16mm_Horizontal
R15: 470; R_Axial_DIN0207_L6.3mm_D2.5mm_P10.16mm_Horizontal
RN5, RN6: RN-9
RN7, RN8: SIL9
RN9: 10k x8; R_Array_SIP9
U$1: PIN_3X8
X1: FABC96R

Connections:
-BUS-EN: IC3.2, JP1.1, X1.C28
-HI-RAM: IC2.20, IC6.10, IC15.2
-IO-RD: IC31.5, X1.B25
-IO-WR: IC31.2, IC31.10, X1.B26
-LO-RAM: IC1.20, IC10.3, IC15.1
-MEM-RD: IC5.1, IC6.5, X1.B23
-MEM-WR: IC6.9, X1.B24
-RESET: IC12.4, IC32.1, IC33.4, X1.C30
-ROM-CS: IC6.12, IC13.20, IC15.13
-TMP-REG-LD0: IC14.1, X1.B28
-TMP-REG-LD1: IC14.13, X1.B30
-TMP-REG-RD0: IC26.1, IC27.1, X1.B27
-TMP-REG-RD1: IC28.1, IC29.1, X1.B29
-VMA: IC3.1, IC7.4, IC14.11, X1.C12
/Sheet 2/RAM0: IC4.1, RN8.2, U$1.17
/Sheet 2/RAM1: IC4.2, RN8.3, U$1.18
/Sheet 2/RAM2: IC4.3, RN8.4, U$1.19
/Sheet 2/RAM3: IC4.4, RN8.5, U$1.20
/Sheet 2/RAM4: IC4.5, RN8.6, U$1.21
/Sheet 2/RAM5: IC4.6, RN8.7, U$1.22
/Sheet 2/RAM6: IC4.11, RN8.8, U$1.23
/Sheet 2/RAM7: IC4.12, RN8.9, U$1.24
/Sheet 2/ROM0: IC18.12, RN7.9, U$1.1
/Sheet 2/ROM1: IC18.11, RN7.8, U$1.2
/Sheet 2/ROM2: IC18.6, RN7.7, U$1.3
/Sheet 2/ROM3: IC18.5, RN7.6, U$1.4
/Sheet 2/ROM4: IC18.4, RN7.5, U$1.5
/Sheet 2/ROM5: IC18.3, RN7.4, U$1.6
/Sheet 2/ROM6: IC18.2, RN7.3, U$1.7
/Sheet 2/ROM7: IC18.1, RN7.2, U$1.8
/Sheet 2/SEL0: IC7.15, U$1.9
/Sheet 2/SEL1: IC7.14, U$1.10
/Sheet 2/SEL2: IC7.13, U$1.11
/Sheet 2/SEL3: IC7.12, U$1.12
/Sheet 2/SEL4: IC7.11, U$1.13
/Sheet 2/SEL5: IC7.10, U$1.14
/Sheet 2/SEL6: IC7.9, U$1.15
/Sheet 2/SEL7: IC7.7, U$1.16
/Sheet 3/ROM-WE: IC13.27, JP3.2
/Sheet 7/-CFOE: IC33.3, IC33.9, IC33.10, IC34.19
/Sheet 7/-CFRESET: IC33.6, J2.1
/Sheet 7/-DASP: J2.39, R12.2
/Sheet 7/-DMACK: J2.29, R13.2
/Sheet 7/-IOR: IC31.6, IC33.1, IC34.1, J2.25
/Sheet 7/-IOW: IC31.8, IC33.2, J2.23
/Sheet 7/-P8SEL: IC30.15, IC31.1
/Sheet 7/-P9SEL: IC30.14, IC31.4, IC31.9
/Sheet 7/-PDIAG: J2.34, R11.2
/Sheet 7/-SRST: IC32.14, IC33.5
/Sheet 7/ACTK: IC33.8, LED1.1
/Sheet 7/CFD0: IC34.18, J2.17, RN9.2
/Sheet 7/CFD1: IC34.17, J2.15, RN9.3
/Sheet 7/CFD2: IC34.16, J2.13, RN9.4
/Sheet 7/CFD3: IC34.15, J2.11, RN9.5
/Sheet 7/CFD4: IC34.14, J2.9, RN9.6
/Sheet 7/CFD5: IC34.13, J2.7, RN9.7
/Sheet 7/CFD6: IC34.12, J2.5, RN9.8
/Sheet 7/CFD7: IC34.11, J2.3, RN9.9
/Sheet 7/DA0: IC32.2, J2.35
/Sheet 7/DA1: IC32.7, J2.33
/Sheet 7/DA2: IC32.10, J2.36
/Sheet 7/IORDY: J2.27, R10.2
/Sheet 7/LATCHCLK: IC31.3, IC32.9
/Sheet 7/LEDA2: LED1.2, R14.2
/Sheet 7/PIN20: J2.20, JP2.2
ADDR0: IC8.2, X1.A3
ADDR1: IC8.4, X1.A4
ADDR2: IC8.6, X1.A5
ADDR3: IC8.8, X1.A6
ADDR4: IC8.11, X1.A7
ADDR5: IC8.13, X1.A8
ADDR6: IC8.15, X1.A9
ADDR7: IC8.17, X1.A10
ADDR8: IC9.2, X1.A11
ADDR9: IC9.4, X1.A12
ADDR10: IC9.6, X1.A13
ADDR11: IC9.8, X1.A14
ADDR12: IC9.11, X1.A15
ADDR13: IC9.13, X1.A16
ADDR14: IC9.15, X1.A17
ADDR15: IC9.17, IC10.4, R15.1, X1.A18
BADDR0: IC1.10, IC2.10, IC8.18, IC13.10
BADDR1: IC1.9, IC2.9, IC8.16, IC13.9
BADDR2: IC1.8, IC2.8, IC8.14, IC13.8
BADDR3: IC1.7, IC2.7, IC8.12, IC13.7
BADDR4: IC1.6, IC2.6, IC8.9, IC13.6
BADDR5: IC1.5, IC2.5, IC8.7, IC13.5
BADDR6: IC1.4, IC2.4, IC8.5, IC13.4
BADDR7: IC1.3, IC2.3, IC8.3, IC13.3
BADDR8: IC1.25, IC2.25, IC9.18, IC13.25
BADDR9: IC1.24, IC2.24, IC9.16, IC13.24
BADDR10: IC1.21, IC2.21, IC9.14, IC13.21
BADDR11: IC1.23, IC2.23, IC9.12, IC13.23
BADDR12: IC1.2, IC2.2, IC7.1, IC11.4, IC13.2
BADDR13: IC1.26, IC2.26, IC7.2, IC11.7
BADDR14: IC1.1, IC2.1, IC7.3, IC11.9
BADDR15: IC7.6, IC11.12, IC14.3
BDATA0: IC1.11, IC2.11, IC5.18, IC13.11
BDATA1: IC1.12, IC2.12, IC5.17, IC13.12
BDATA2: IC1.13, IC2.13, IC5.16, IC13.13
BDATA3: IC1.15, IC2.15, IC5.15, IC13.15
BDATA4: IC1.16, IC2.16, IC5.14, IC13.16
BDATA5: IC1.17, IC2.17, IC5.13, IC13.17
BDATA6: IC1.18, IC2.18, IC5.12, IC13.18
BDATA7: IC1.19, IC2.19, IC5.11, IC13.19
DATA0: IC5.2, IC26.2, IC26.3, IC28.2, IC28.3, IC32.4, IC34.2, RN5.2, X1.A19
DATA1: IC5.3, IC26.4, IC26.5, IC28.4, IC28.5, IC32.5, IC34.3, RN5.3, X1.A20
DATA2: IC5.4, IC26.6, IC26.7, IC28.6, IC28.7, IC32.12, IC34.4, RN5.4, X1.A21
DATA3: IC5.5, IC26.8, IC26.9, IC28.8, IC28.9, IC32.13, IC34.5, RN5.5, X1.A22
DATA4: IC5.6, IC26.12, IC26.13, IC28.12, IC28.13, IC34.6, RN5.6, X1.A23
DATA5: IC5.7, IC26.14, IC26.15, IC28.14, IC28.15, IC34.7, RN5.7, X1.A24
DATA6: IC5.8, IC26.16, IC26.17, IC28.16, IC28.17, IC34.8, RN5.8, X1.A25
DATA7: IC5.9, IC26.18, IC26.19, IC28.18, IC28.19, IC34.9, RN5.9, X1.A26
DATA8: IC27.2, IC27.3, IC29.2, IC29.3, RN6.2, X1.A27
DATA9: IC27.4, IC27.5, IC29.4, IC29.5, RN6.3, X1.A28
DATA10: IC27.6, IC27.7, IC29.6, IC29.7, RN6.4, X1.A29
DATA11: IC27.8, IC27.9, IC29.8, IC29.9, RN6.5, X1.A30
DATA12: IC27.12, IC27.13, IC29.12, IC29.13, RN6.6, X1.B3
DATA13: IC27.14, IC27.15, IC29.14, IC29.15, RN6.7, X1.B4
DATA14: IC27.16, IC27.17, IC29.16, IC29.17, RN6.8, X1.B5
DATA15: IC27.18, IC27.19, IC29.18, IC29.19, RN6.9, X1.B6
FORCE-ROM: IC11.1, IC12.5
GND: C1.2, C2.2, C3.2, C4.2, C5.2, C6.2, C7.2, C8.2, C9.2, C10.2, C11.2, C12.2, C13.2, C14.2, C15.2, C16.2, C17.2, C18.2, C19.1, C24.1, C25.2, C26.2, C27.2, C28.2, C29.2, C30.2, IC1.14, IC2.14, IC3.4, IC3.5, IC3.7, IC3.9, IC3.10, IC3.12, IC3.13, IC4.7, IC5.10, IC6.7, IC7.8, IC8.1, IC8.10, IC8.19, IC9.1, IC9.10, IC9.19, IC10.7, IC11.8, IC11.15, IC12.2, IC12.7, IC12.10, IC12.11, IC12.12, IC12.13, IC13.14, IC14.7, IC15.3, IC15.4, IC15.5, IC15.7, IC15.9, IC15.10, IC15.11, IC18.7, IC26.10, IC27.10, IC28.10, IC29.10, IC30.4, IC30.5, IC30.8, IC31.7, IC31.12, IC31.13, IC32.8, IC33.7, IC33.12, IC33.13, IC34.10, J2.2, J2.19, J2.22, J2.24, J2.26, J2.28, J2.30, J2.37, J2.40, J3.2, J3.3, JP1.3, PWR0.K, R15.2, RN5.1, RN6.1, X1.A1, X1.A32, X1.B1, X1.B32, X1.C1, X1.C32
IO-ADDR0: IC30.1, X1.C7
IO-ADDR1: IC30.2, X1.C8
IO-ADDR2: IC30.3, X1.C9
IO-ADDR3: IC30.6, X1.C10
unnamed: IC1.22, IC2.22, IC6.2, IC13.22
unnamed: IC1.27, IC2.27, IC6.4, JP3.1
unnamed: IC4.8, IC6.11
unnamed: IC6.1, IC6.6
unnamed: IC6.3, IC6.8
unnamed: IC7.5, JP1.2
unnamed: IC10.1, IC14.4
unnamed: IC10.2, IC14.10
unnamed: IC10.5, IC10.11
unnamed: IC10.6, IC10.9, IC10.10
unnamed: IC10.8, IC12.3
unnamed: IC3.3, IC10.12, IC10.13
unnamed: IC9.9, IC11.2
unnamed: IC9.7, IC11.5
unnamed: IC9.5, IC11.11
unnamed: IC9.3, IC11.14
unnamed: IC14.2, IC26.11, IC27.11
unnamed: IC14.12, IC28.11, IC29.11
unnamed: IC5.19, IC15.12
unnamed: IC6.13, IC18.8
unnamed: PWR0.A, R2.1
VCC: C1.1, C2.1, C3.1, C4.1, C5.1, C6.1, C7.1, C8.1, C9.1, C10.1, C11.1, C12.1, C13.1, C14.1, C15.1, C16.1, C17.1, C18.1, C19.2, C24.2, C25.1, C26.1, C27.1, C28.1, C29.1, C30.1, IC1.28, IC2.28, IC3.14, IC4.14, IC5.20, IC6.14, IC7.16, IC8.20, IC9.20, IC10.14, IC11.3, IC11.6, IC11.10, IC11.13, IC11.16, IC12.1, IC12.14, IC13.28, IC14.14, IC15.14, IC18.14, IC26.20, IC27.20, IC28.20, IC29.20, IC30.16, IC31.14, IC32.16, IC33.14, IC34.20, J2.38, J3.1, JP2.1, JP3.3, R2.2, R10.1, R11.1, R12.1, R13.1, R14.1, RN7.1, RN8.1, RN9.1, X1.A2, X1.A31, X1.B2, X1.B31, X1.C2, X1.C31

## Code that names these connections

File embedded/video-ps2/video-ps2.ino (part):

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   video-ps2 (2026-10-22) - the PS/2 keyboard and mouse controller of the YACC1 video card V2.0
   (hardware/cards/video/kicad/v2.0, BACKLOG "Video card V2.0", embedded/video-ps2/README.md).
   Revised 2026-10-22 after the design review (hardware/cards/video/reviews/v2.0.md): BUSY and SRC swapped (V2-1,
   Optiboot's LED pin PB5 is now the SRC output), host-to-device bit count (V2-3), LDDATA idle high (V2-7), MD released
   with pull-ups (V2-9), the V2-18 robustness items. 2026-10-23 after the re-review (hardware/cards/video/reviews/v2.0-r2.md
   R2-10): ps2_wait() takes only reply bytes; a key typed while a command waits for its answer goes to the key queue.

   An ATmega328P at 16 MHz between two PS/2 jacks and the YACC1 bus. The CPU never talks to it directly: it reads and
   writes three latches on the card (so a 1 MHz CPU never waits for this firmware):
     IN PE   a 74LS374 the firmware loads (MD0..7 + LDDATA); loading it sets FULL, the CPU's read clears FULL
     IN PD   status (a 74LS244): bit 0 FULL, bit 1 SRC (this pin: 0 keyboard, 1 mouse), bit 2 BUSY
     OUT PD  a 74LS374 the CPU loads (sets BUSY); the firmware reads it onto MD0..7 with -RDCMD, which clears BUSY

   Pins (Arduino Uno numbering = the ATmega328P's port pins):
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     D3        PD3 INT1              mouse CLOCK (J3 pin 5)
     D4        PD4                   keyboard DATA (J2 pin 1)
     D5        PD5                   mouse DATA (J3 pin 1)
     D6        PD6  LDDATA  out      idle high (10k pull-up R22); a low pulse: the data latch takes MD0..7 and FULL
                                     sets on its rising edge
     D7        PD7  -RDCMD  out      low: the command latch drives MD0..7 (and BUSY clears); 10k pull-up R23
     A0..A5    PC0..PC5  MD0..MD5    the local bus (both directions)
     D8, D9    PB0, PB1  MD6, MD7
     D10       PB2  FULL    in       1 = the CPU has not read the last byte yet
     D11       PB3  BUSY    in       1 = the CPU wrote a command (OUT PD) the firmware has not read yet
     D12       PB4  INTREQ  out      1 = request -INT: the card ANDs it with FULL (IC54/B) into IC27/D (open
                                     collector) and jumper JP3 INT-EN; 10k pull-down R24
     D13       PB5  SRC     out      0 = the byte in the data latch is from the keyboard, 1 = from the mouse
                                     (PB5 is the Uno bootloader's LED pin: it may flash during Optiboot, harmless on
                                     SRC, which only matters with FULL)
   The PS/2 lines are open drain: a pin is either an input (the 4.7k pull-up makes 1) or an output driving 0.
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   whole (a packet is queued only when all three bytes are in).
*/

#define KCLK 2
#define MCLK 3
#define KDAT 4
#define MDAT 5
#define LDDATA 6
#define RDCMD 7
#define PIN_FULL 10
#define PIN_BUSY 11                    // V2-1: BUSY on PB3, SRC on PB5 (Optiboot's LED pin)
#define PIN_INTREQ 12
#define PIN_SRC 13

#define QSIZE 64                      // the queue to the CPU: (byte, source) pairs
#define RXSIZE 64                     // each port's receive ring (64: the mouse's packets during LED commands)
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}

void feed_cpu() {                                 // the next queued byte into the data latch once the CPU took the last
  if (qh == qt || digitalRead(PIN_FULL)) return;
  delayMicroseconds(5);                           // FULL is held clear while the CPU's read strobe lasts: INP holds
  if (digitalRead(PIN_FULL)) return;              // -IO-RD 7 clocks (7 us at 1 MHz); a load inside it is caught below
  digitalWrite(PIN_SRC, qsrc[qt]);
  md_write(qbyte[qt]);
  delayMicroseconds(1);
  digitalWrite(LDDATA, LOW);                      // LDDATA idles high (V2-7): a low pulse,
  delayMicroseconds(1);
  digitalWrite(LDDATA, HIGH);                     // the 74LS374 and FULL take the byte on its rising edge
  md_release();
  if (digitalRead(PIN_FULL)) qt = (qt + 1) % QSIZE;   // else a read strobe overlapped: load it again next time
}

// ---------------------------------------------------------------- keyboard: set-2 scan codes -> ASCII
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
void setup() {
  Serial.begin(38400);
  pinMode(KCLK, INPUT); pinMode(KDAT, INPUT); pinMode(MCLK, INPUT); pinMode(MDAT, INPUT);   // released: the pull-ups
  digitalWrite(LDDATA, HIGH); pinMode(LDDATA, OUTPUT);     // idle high, as the pull-up held it through the reset
  digitalWrite(RDCMD, HIGH); pinMode(RDCMD, OUTPUT);
  pinMode(PIN_FULL, INPUT); pinMode(PIN_BUSY, INPUT);
  pinMode(PIN_SRC, OUTPUT); pinMode(PIN_INTREQ, OUTPUT); digitalWrite(PIN_INTREQ, LOW);
  md_release();
  attachInterrupt(digitalPinToInterrupt(KCLK), kb_isr, FALLING);
  attachInterrupt(digitalPinToInterrupt(MCLK), ms_isr, FALLING);
  Serial.println(F("video-ps2 2026-10-23"));
  if (digitalRead(PIN_BUSY)) read_command();      // a command latched before a reset: dropped
  start_all();
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  while ((b = ps2_next(ms)) >= 0) mouse_byte(b);
  if (digitalRead(PIN_BUSY)) command(read_command());
  feed_cpu();
  digitalWrite(PIN_INTREQ, int_on && !acked && digitalRead(PIN_FULL));
}

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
